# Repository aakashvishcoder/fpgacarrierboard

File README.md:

# FPGA Carrier Board

KiCad 10 design for an FPGA carrier board built around a Xilinx Artix-7
XC7A35T-FGG484.

## Status

Schematic complete, ERC clean (0 errors), BOM complete (56 lines). PCB
layout has not started yet.

## Sheets

| Sheet file | Contents |
|---|---|
| `powerrails.kicad_sch` | 4x TPS62130A regulators (1V0, 1V8, 1V2, 3V3) |
| `powerin.kicad_sch` | USB-C input, eFuse (TPS259251), protection |
| `fpgacore.kicad_sch` | XC7A35T-FGG484 (7 units A-G), MGT power filtering |
| `dcapacitors.kicad_sch` | FPGA decoupling capacitors (nested under FPGA Core) |
| `config_jtag.kicad_sch` | SPI flash (W25Q128), JTAG header, boot straps |
| `clocks.kicad_sch` | Y1 50 MHz system clock |
| `ethernet1g.kicad_sch` | RTL8211E-VB-CG PHY, RJ45 (HR911130C), Y3 25 MHz oscillator |
| `sfplane.kicad_sch` | Samtec SFPK-SL (SFP+ cage/connector kit), AC-coupling caps |
| `iobreakout.kicad_sch` | LEDs, buttons, spare-I/O header |

## Key parts (LCSC)

| Ref | Part | LCSC |
|---|---|---|
| U1-4 | TPS62130A | C337502 |
| U5 | eFuse | C527680 |
| U6 | XC7A35T-FGG484 | C6934285 |
| U7 | W25Q128 flash | C97521 |
| U8 | RTL8211E-VB-CG | C90735 |
| USB1 | USB-C connector | C456012 |
| J3 | RJ45 (HR911130C) | C50933 |
| J4 | SFPK-SL | C20691304 |
| L1-4 | Inductor | C719179 |
| Y1 | 50 MHz oscillator | C717684 |
| Y3 | 25 MHz oscillator | C669088 |
| J2 | SMA connector | C2693814 |

## Assembly split

JLC handles placement of ICs, the FPGA BGA, QFN parts, and decoupling
capacitors. Connectors, resistors, LEDs, the zener, the fuse, and test
points are hand-soldered as through-hole parts (not SMD) so they can be
assembled without reflow equipment. The 10µF/22µF bulk filter caps are
through-hole electrolytics; everything else hand-soldered is through-hole
ceramic, resistor, or LED.

## Generating the BOM

The GUI "Generate Bill of Materials" and Symbol Fields Table exporters are
unreliable in this KiCad build and can silently produce empty or partial
output. Use `kicad-cli` instead:

```bash
kicad-cli sch export bom \
  --output bom_cli.csv \
  --fields "Reference,Value,Footprint,QUANTITY,LCSC Part" \
  --labels "Reference,Value,Footprint,Qty,LCSC" \
  --group-by "Value,Footprint" \
  fpgacarrierboard.kicad_sch
```

## Libraries

Custom/imported symbol and footprint libraries live in `~/kicad-libs/`
(EasyEDA imports, Samtec parts, SFPK-SL, etc.), registered in the local
`sym-lib-table` and `fp-lib-table`.

## Next step

PCB layout: board outline, 6-layer stackup for BGA fanout and
controlled-impedance pairs (RGMII, SFP+ differential pairs), part
placement, and routing.

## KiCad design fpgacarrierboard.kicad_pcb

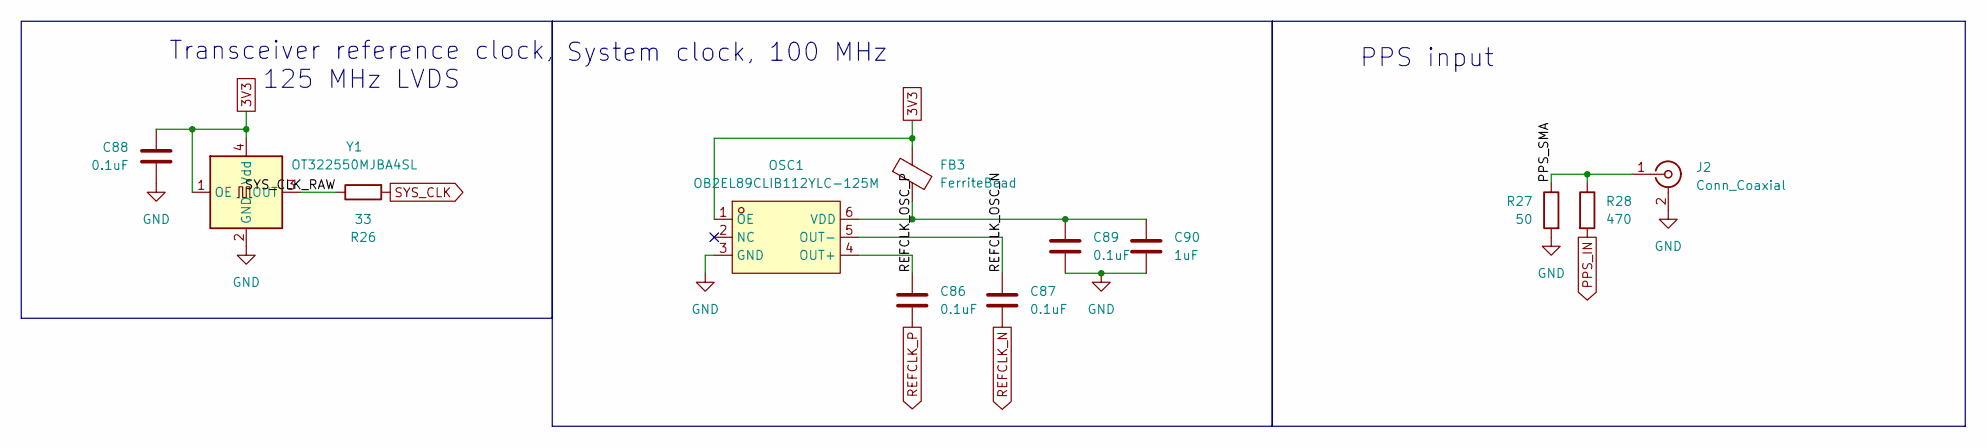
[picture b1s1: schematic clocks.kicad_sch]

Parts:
C86, C87: 0.1uF; C_0603_1608Metric; LCSC Part C14663
C88, C89: 0.1uF; C_Disc_D3.0mm_W2.0mm_P2.50mm; LCSC Part C5632430
C90: 1uF; C_Disc_D3.0mm_W2.0mm_P2.50mm; LCSC Part C1646109
FB3: FerriteBead; L_0603_1608Metric; LCSC Part C19330
J2: Conn_Coaxial; SMA_Amphenol_132134-10_Vertical; LCSC Part C2693814
OSC1: OB2EL89CLIB112YLC-125M; OSC-SMD_6P-L3.2-W2.5-BL-1; MPN OB2EL89CLIB112YLC-125M; LCSC Part C7425465
R26: 33; R_Axial_DIN0207_L6.3mm_D2.5mm_P10.16mm_Horizontal
R27: 50; R_Axial_DIN0207_L6.3mm_D2.5mm_P10.16mm_Horizontal
R28: 470; R_Axial_DIN0207_L6.3mm_D2.5mm_P10.16mm_Horizontal
Y1: OT322550MJBA4SL; OSC-SMD_4P-L3.2-W2.5-BL; LCSC Part C717684

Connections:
3V3: C88.1, FB3.1, OSC1.1 (OE), Y1.1 (OE), Y1.4 (Vdd); also elsewhere on the board
/Clocks/PPS_SMA: J2.1 (In), R27.1, R28.1
/Clocks/REFCLK_OSC_N: C87.1, OSC1.5 (OUT-)
/Clocks/REFCLK_OSC_P: C86.1, OSC1.4 (OUT+)
/Clocks/SYS_CLK_RAW: R26.1, Y1.3 (OUT)
GND: C88.2, C89.2, C90.2, J2.2 (Ext), OSC1.3 (GND), R27.2, Y1.2 (GND); also elsewhere on the board
unnamed: C89.1, C90.1, FB3.2, OSC1.6 (VDD)
PPS_IN: R28.2; also elsewhere on the board
REFCLK_N: C87.2; also elsewhere on the board
REFCLK_P: C86.2; also elsewhere on the board
SYS_CLK: R26.2; also elsewhere on the board

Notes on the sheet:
System clock, 100 MHz
PPS input
Transceiver reference clock, 125 MHz LVDS

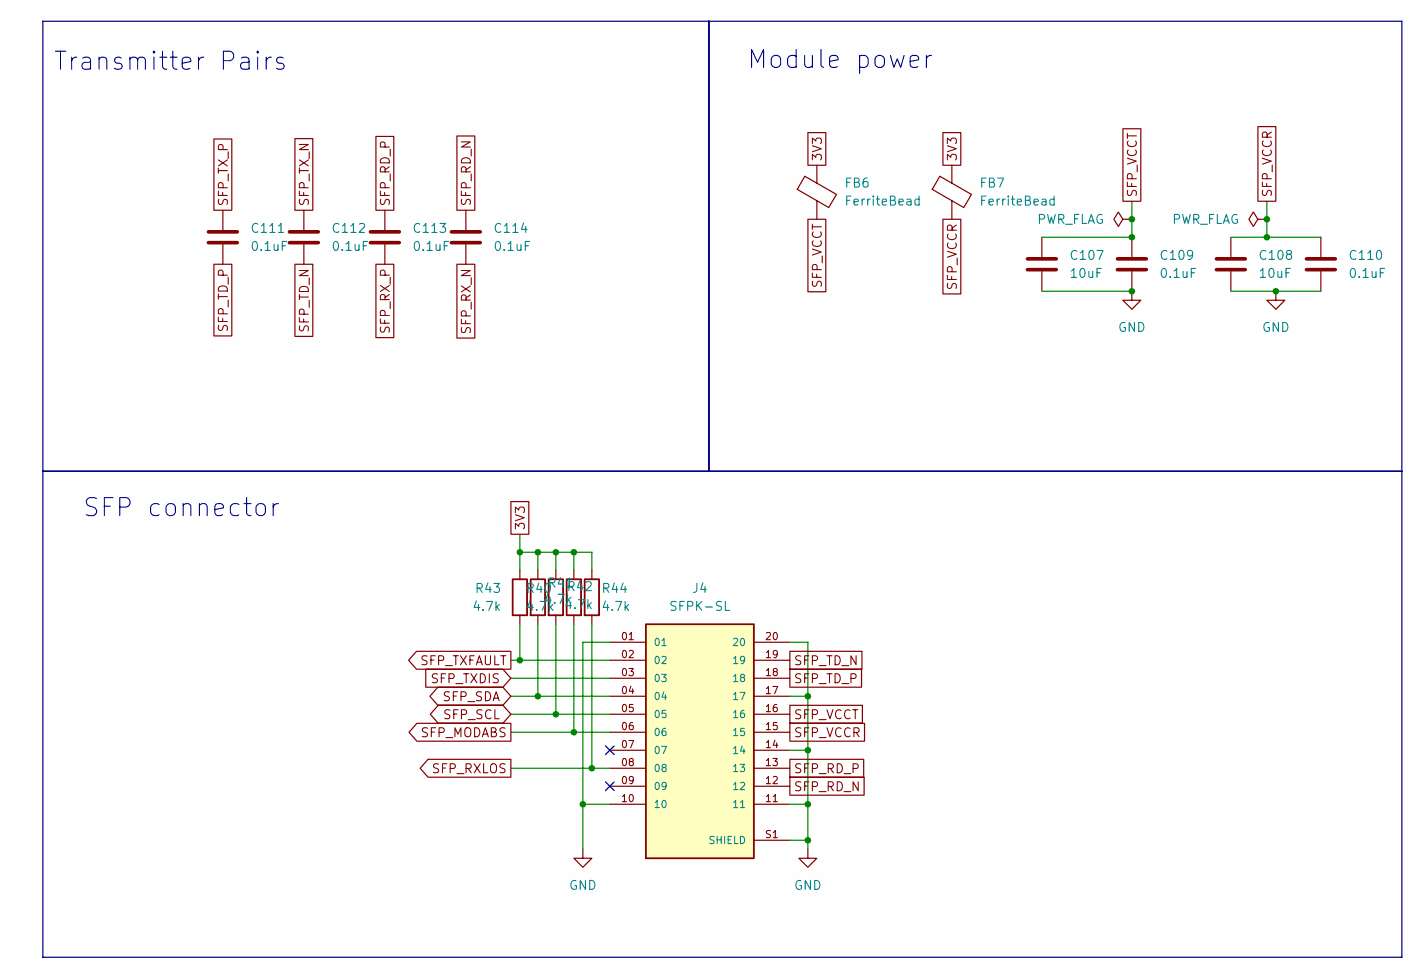
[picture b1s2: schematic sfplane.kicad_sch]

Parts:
C107, C108: 10uF; CP_Radial_D5.0mm_P2.00mm; LCSC Part C47344176
C109, C110: 0.1uF; C_Disc_D3.0mm_W2.0mm_P2.50mm; LCSC Part C5632430
C111, C112, C113, C114: 0.1uF; C_0603_1608Metric; LCSC Part C14663
FB6, FB7: FerriteBead; L_0603_1608Metric; LCSC Part C19330
J4: SFPK-SL; SAMTEC_SFPK-SL; PARTREV H; LCSC Part C20691304
R40, R41, R42, R43, R44: 4.7k; R_Axial_DIN0207_L6.3mm_D2.5mm_P10.16mm_Horizontal

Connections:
3V3: FB6.1, FB7.1, R40.1, R41.1, R42.1, R43.1, R44.1; also elsewhere on the board
GND: C107.2, C108.2, C109.2, C110.2, J4.01, J4.10, J4.11, J4.14, J4.17, J4.20, J4.S1 (SHIELD), J4.S2 (SHIELD), J4.S3 (SHIELD), J4.S4 (SHIELD), J4.S5 (SHIELD), J4.S6 (SHIELD), J4.S7 (SHIELD), J4.S8 (SHIELD), J4.S9 (SHIELD), J4.S10 (SHIELD), J4.S11 (SHIELD), J4.S12 (SHIELD), J4.S13 (SHIELD), J4.S14 (SHIELD), J4.S15 (SHIELD), J4.S16 (SHIELD), J4.S17 (SHIELD); also elsewhere on the board
SFP_MODABS: J4.06, R42.2; also elsewhere on the board
SFP_RD_N: C114.1, J4.12
SFP_RD_P: C113.1, J4.13
SFP_RXLOS: J4.08, R44.2; also elsewhere on the board
SFP_RX_N: C114.2; also elsewhere on the board
SFP_RX_P: C113.2; also elsewhere on the board
SFP_SCL: J4.05, R41.2; also elsewhere on the board
SFP_SDA: J4.04, R40.2; also elsewhere on the board
SFP_TD_N: C112.2, J4.19
SFP_TD_P: C111.2, J4.18
SFP_TXDIS: J4.03; also elsewhere on the board
SFP_TXFAULT: J4.02, R43.2; also elsewhere on the board
SFP_TX_N: C112.1; also elsewhere on the board
SFP_TX_P: C111.1; also elsewhere on the board
SFP_VCCR: C108.1, C110.1, FB7.2, J4.15
SFP_VCCT: C107.1, C109.1, FB6.2, J4.16

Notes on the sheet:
Transmitter Pairs
SFP connector
Module power

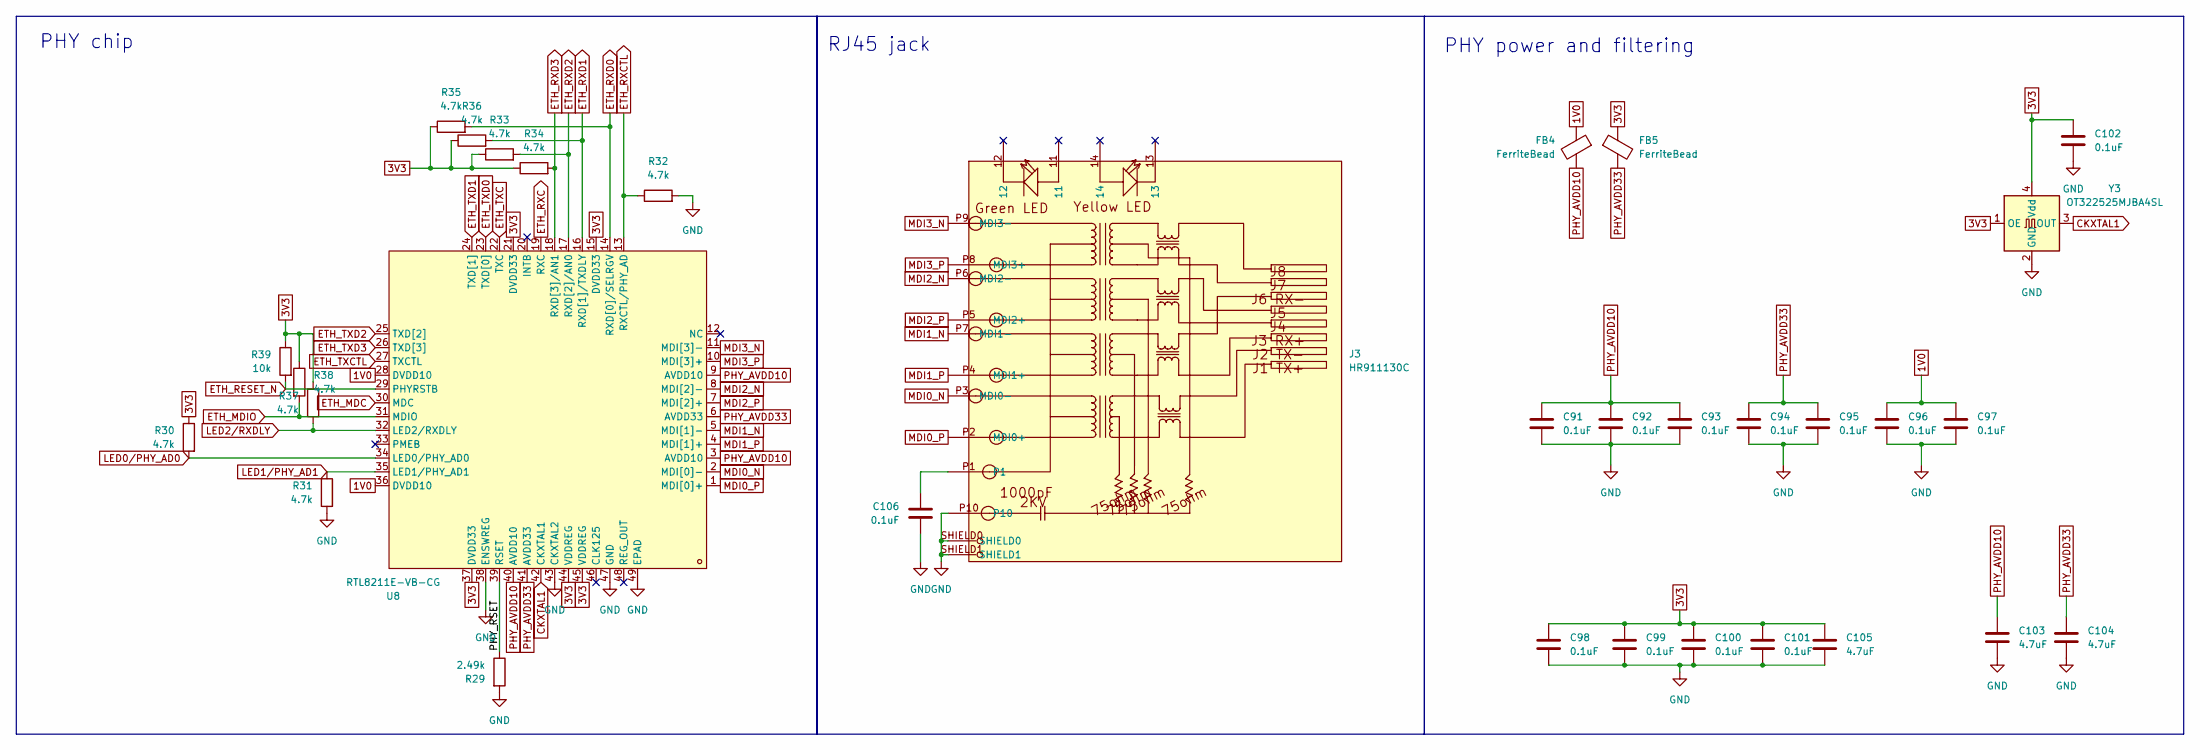
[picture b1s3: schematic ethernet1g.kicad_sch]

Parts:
C91, C92, C93, C94, C95, C96, C97, C98, C99, C100, C101, C102: 0.1uF; C_0603_1608Metric; LCSC Part C14663
C103, C104, C105: 4.7uF; C_0805_2012Metric; LCSC Part C98195
C106: 0.1uF; C_Disc_D3.0mm_W2.0mm_P2.50mm; LCSC Part C5632430
FB4, FB5: FerriteBead; L_0603_1608Metric; LCSC Part C19330
J3: HR911130C; RJ45-TH_HR911130C; MPN HR911130C; LCSC Part C50933
R29: 2.49k; R_0603_1608Metric; LCSC Part C2930072
R30, R31, R32, R33, R34, R35, R36, R37, R38: 4.7k; R_Axial_DIN0207_L6.3mm_D2.5mm_P10.16mm_Horizontal
R39: 10k; R_Axial_DIN0207_L6.3mm_D2.5mm_P10.16mm_Horizontal
U8: RTL8211E-VB-CG; QFN-48_L6.0-W6.0-P0.40-BL-EP3.8; MPN RTL8211E-VB-CG; LCSC Part C90735
Y3: OT322525MJBA4SL; OSC-SMD_4P-L3.2-W2.5-BL; LCSC Part C669088

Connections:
1V0: C96.1, C97.1, FB4.1, U8.28 (DVDD10), U8.36 (DVDD10); also elsewhere on the board
3V3: C98.1, C99.1, C100.1, C101.1, C102.1, C105.1, FB5.1, R30.1, R33.1, R34.1, R35.1, R36.1, R37.1, R38.1, R39.1, U8.15 (DVDD33), U8.21 (DVDD33), U8.37 (DVDD33), U8.44 (VDDREG), U8.45 (VDDREG), Y3.1 (OE), Y3.4 (Vdd); also elsewhere on the board
/Ethernet_1G/PHY_RSET: R29.1, U8.39 (RSET)
CKXTAL1: U8.42 (CKXTAL1), Y3.3 (OUT)
ETH_MDC: U8.30 (MDC); also elsewhere on the board
ETH_MDIO: R38.2, U8.31 (MDIO); also elsewhere on the board
ETH_RESET_N: R39.2, U8.29 (PHYRSTB); also elsewhere on the board
ETH_RXC: U8.19 (RXC); also elsewhere on the board
ETH_RXCTL: R32.1, U8.13 (RXCTL/PHY_AD); also elsewhere on the board
ETH_RXD0: R35.2, U8.14 (RXD[0]/SELRGV); also elsewhere on the board
ETH_RXD1: R36.2, U8.16 (RXD[1]/TXDLY); also elsewhere on the board
ETH_RXD2: R33.2, U8.17 (RXD[2]/AN0); also elsewhere on the board
ETH_RXD3: R34.2, U8.18 (RXD[3]/AN1); also elsewhere on the board
ETH_TXC: U8.22 (TXC); also elsewhere on the board
ETH_TXCTL: U8.27 (TXCTL); also elsewhere on the board
ETH_TXD0: U8.23 (TXD[0]); also elsewhere on the board
ETH_TXD1: U8.24 (TXD[1]); also elsewhere on the board
ETH_TXD2: U8.25 (TXD[2]); also elsewhere on the board
ETH_TXD3: U8.26 (TXD[3]); also elsewhere on the board
GND: C91.2, C92.2, C93.2, C94.2, C95.2, C96.2, C97.2, C98.2, C99.2, C100.2, C101.2, C102.2, C103.2, C104.2, C105.2, C106.2, J3.P10, J3.SHIELD0, J3.SHIELD1, R29.2, R31.2, R32.2, U8.38 (ENSWREG), U8.43 (CKXTAL2), U8.47 (GND), U8.49 (EPAD), Y3.2 (GND); also elsewhere on the board
LED0/PHY_AD0: R30.2, U8.34 (LED0/PHY_AD0)
LED1/PHY_AD1: R31.1, U8.35 (LED1/PHY_AD1)
LED2/RXDLY: R37.2, U8.32 (LED2/RXDLY)
MDI0_N: J3.P3 (MDI0-), U8.2 (MDI[0]-)
MDI0_P: J3.P2 (MDI0+), U8.1 (MDI[0]+)
MDI1_N: J3.P7 (MDI1-), U8.5 (MDI[1]-)
MDI1_P: J3.P4 (MDI1+), U8.4 (MDI[1]+)
MDI2_N: J3.P6 (MDI2-), U8.8 (MDI[2]-)
MDI2_P: J3.P5 (MDI2+), U8.7 (MDI[2]+)
MDI3_N: J3.P9 (MDI3-), U8.11 (MDI[3]-)
MDI3_P: J3.P8 (MDI3+), U8.10 (MDI[3]+)
unnamed: C106.1, J3.P1
PHY_AVDD10: C91.1, C92.1, C93.1, C103.1, FB4.2, U8.3 (AVDD10), U8.9 (AVDD10), U8.40 (AVDD10)
PHY_AVDD33: C94.1, C95.1, C104.1, FB5.2, U8.6 (AVDD33), U8.41 (AVDD33)

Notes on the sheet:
PHY chip
PHY power and filtering
RJ45 jack

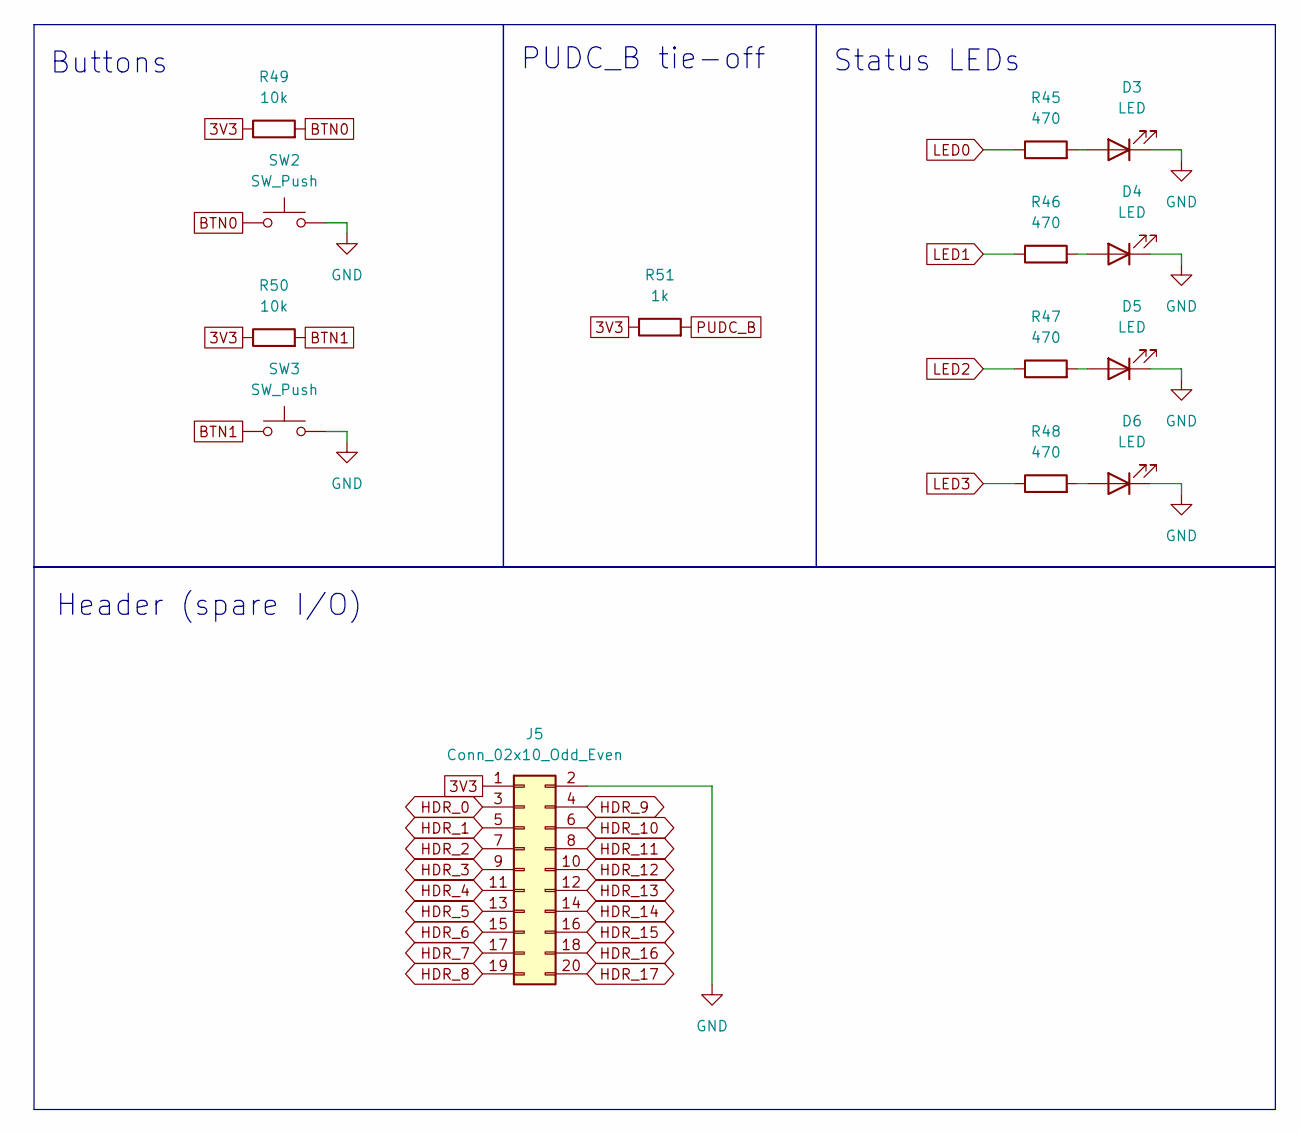
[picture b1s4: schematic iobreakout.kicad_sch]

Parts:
D3, D4, D5, D6: LED; LED_D3.0mm
J5: Conn_02x10_Odd_Even; PinHeader_2x10_P2.54mm_Vertical
R45, R46, R47, R48: 470; R_Axial_DIN0207_L6.3mm_D2.5mm_P10.16mm_Horizontal
R49, R50: 10k; R_Axial_DIN0207_L6.3mm_D2.5mm_P10.16mm_Horizontal
R51: 1k; R_Axial_DIN0207_L6.3mm_D2.5mm_P10.16mm_Horizontal
SW2, SW3: SW_Push; SW_SPST_TL3342

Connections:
3V3: J5.1, R49.1, R50.1, R51.1; also elsewhere on the board
BTN0: R49.2, SW2.1; also elsewhere on the board
BTN1: R50.2, SW3.1; also elsewhere on the board
GND: D3.1 (K), D4.1 (K), D5.1 (K), D6.1 (K), J5.2, SW2.2, SW3.2; also elsewhere on the board
HDR_0: J5.3; also elsewhere on the board
HDR_1: J5.5; also elsewhere on the board
HDR_2: J5.7; also elsewhere on the board
HDR_3: J5.9; also elsewhere on the board
HDR_4: J5.11; also elsewhere on the board
HDR_5: J5.13; also elsewhere on the board
HDR_6: J5.15; also elsewhere on the board
HDR_7: J5.17; also elsewhere on the board
HDR_8: J5.19; also elsewhere on the board
HDR_9: J5.4; also elsewhere on the board
HDR_10: J5.6; also elsewhere on the board
HDR_11: J5.8; also elsewhere on the board
HDR_12: J5.10; also elsewhere on the board
HDR_13: J5.12; also elsewhere on the board
HDR_14: J5.14; also elsewhere on the board
HDR_15: J5.16; also elsewhere on the board
HDR_16: J5.18; also elsewhere on the board
HDR_17: J5.20; also elsewhere on the board
LED0: R45.1; also elsewhere on the board
LED1: R46.1; also elsewhere on the board
LED2: R47.1; also elsewhere on the board
LED3: R48.1; also elsewhere on the board
unnamed: D3.2 (A), R45.2
unnamed: D4.2 (A), R46.2
unnamed: D5.2 (A), R47.2
unnamed: D6.2 (A), R48.2
PUDC_B: R51.2; also elsewhere on the board

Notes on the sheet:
Buttons
PUDC_B tie-off
Status LEDs
Header (spare I/O)

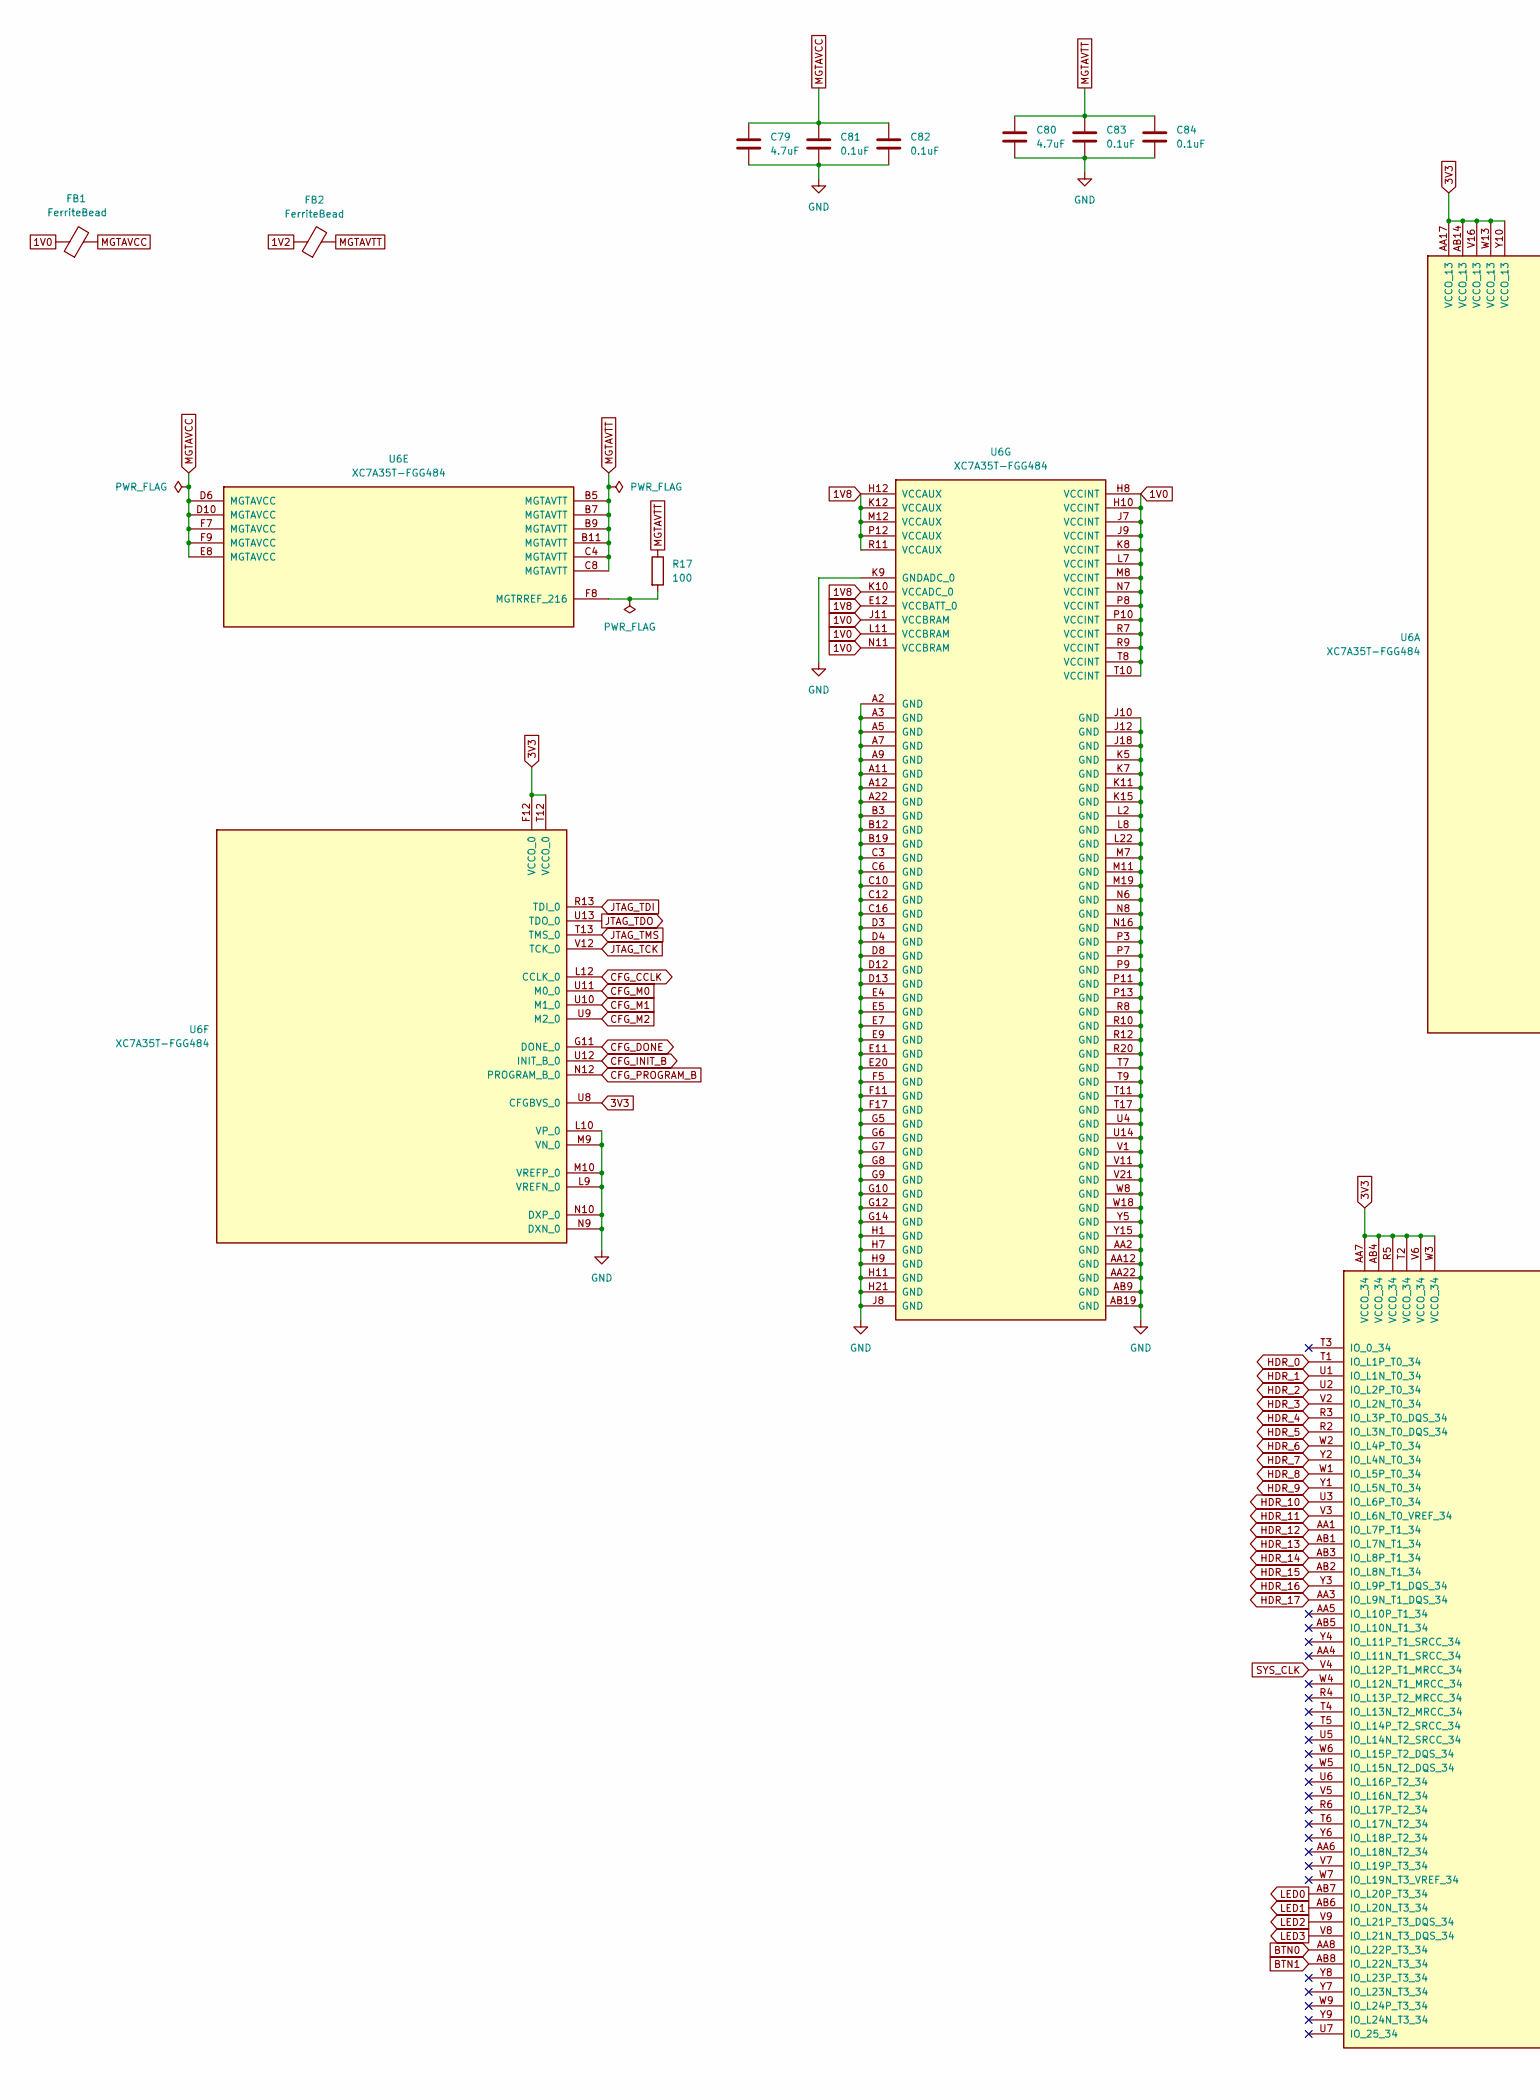
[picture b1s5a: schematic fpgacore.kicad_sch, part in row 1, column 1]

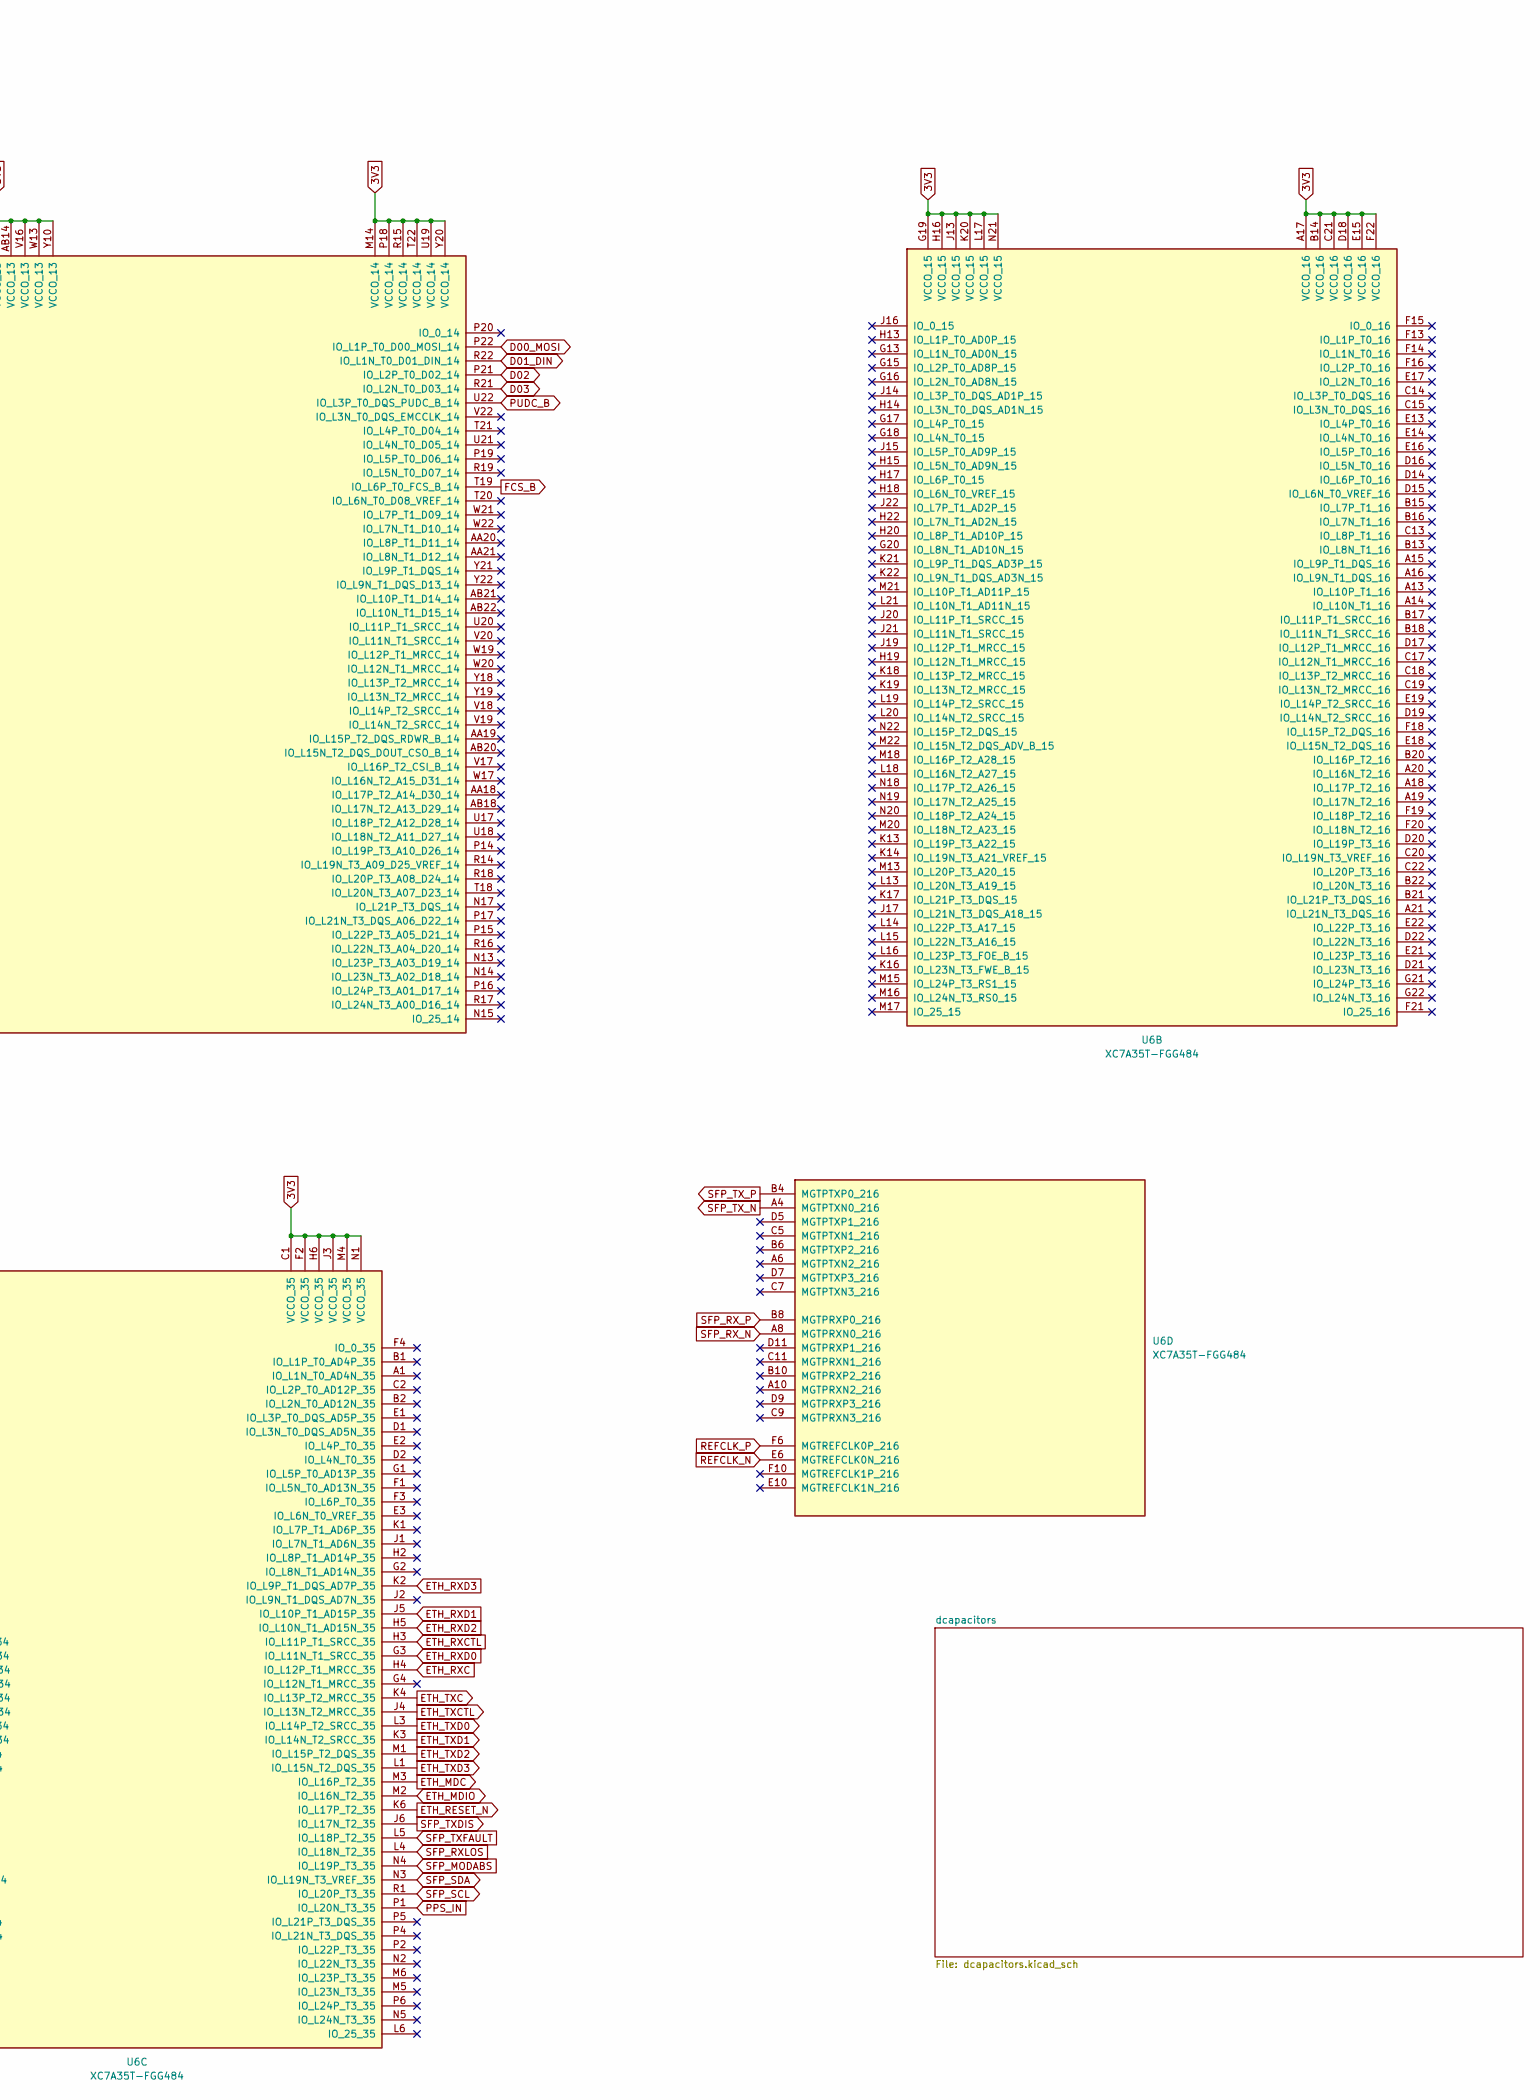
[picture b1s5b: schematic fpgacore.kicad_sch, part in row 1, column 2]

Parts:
C79, C80: 4.7uF; C_0603_1608Metric; LCSC Part C107368
C81, C82, C83, C84: 0.1uF; C_0603_1608Metric; LCSC Part C14663
FB1, FB2: FerriteBead; L_0603_1608Metric; LCSC Part C19330
R17: 100; R_0603_1608Metric; LCSC Part C2906981
U6: XC7A35T-FGG484; Xilinx_FGG484; LCSC Part C6934285

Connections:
1V0: FB1.1, U6.H8 (VCCINT), U6.H10 (VCCINT), U6.J7 (VCCINT), U6.J9 (VCCINT), U6.J11 (VCCBRAM), U6.K8 (VCCINT), U6.L7 (VCCINT), U6.L11 (VCCBRAM), U6.M8 (VCCINT), U6.N7 (VCCINT), U6.N11 (VCCBRAM), U6.P8 (VCCINT), U6.P10 (VCCINT), U6.R7 (VCCINT), U6.R9 (VCCINT), U6.T8 (VCCINT), U6.T10 (VCCINT); also elsewhere on the board
1V2: FB2.1; also elsewhere on the board
1V8: U6.E12 (VCCBATT_0), U6.H12 (VCCAUX), U6.K10 (VCCADC_0), U6.K12 (VCCAUX), U6.M12 (VCCAUX), U6.P12 (VCCAUX), U6.R11 (VCCAUX); also elsewhere on the board
3V3: U6.A17 (VCCO_16), U6.AA7 (VCCO_34), U6.AA17 (VCCO_13), U6.AB4 (VCCO_34), U6.AB14 (VCCO_13), U6.B14 (VCCO_16), U6.C1 (VCCO_35), U6.C21 (VCCO_16), U6.D18 (VCCO_16), U6.E15 (VCCO_16), U6.F2 (VCCO_35), U6.F12 (VCCO_0), U6.F22 (VCCO_16), U6.G19 (VCCO_15), U6.H6 (VCCO_35), U6.H16 (VCCO_15), U6.J3 (VCCO_35), U6.J13 (VCCO_15), U6.K20 (VCCO_15), U6.L17 (VCCO_15), U6.M4 (VCCO_35), U6.M14 (VCCO_14), U6.N1 (VCCO_35), U6.N21 (VCCO_15), U6.P18 (VCCO_14), U6.R5 (VCCO_34), U6.R15 (VCCO_14), U6.T2 (VCCO_34), U6.T12 (VCCO_0), U6.T22 (VCCO_14), U6.U8 (CFGBVS_0), U6.U19 (VCCO_14), U6.V6 (VCCO_34), U6.V16 (VCCO_13), U6.W3 (VCCO_34), U6.W13 (VCCO_13), U6.Y10 (VCCO_13), U6.Y20 (VCCO_14); also elsewhere on the board
BTN0: U6.AA8 (IO_L22P_T3_34); also elsewhere on the board
BTN1: U6.AB8 (IO_L22N_T3_34); also elsewhere on the board
CFG_CCLK: U6.L12 (CCLK_0); also elsewhere on the board
CFG_DONE: U6.G11 (DONE_0); also elsewhere on the board
CFG_INIT_B: U6.U12 (INIT_B_0); also elsewhere on the board
CFG_M0: U6.U11 (M0_0); also elsewhere on the board
CFG_M1: U6.U10 (M1_0); also elsewhere on the board
CFG_M2: U6.U9 (M2_0); also elsewhere on the board
CFG_PROGRAM_B: U6.N12 (PROGRAM_B_0); also elsewhere on the board
D00_MOSI: U6.P22 (IO_L1P_T0_D00_MOSI_14); also elsewhere on the board
D01_DIN: U6.R22 (IO_L1N_T0_D01_DIN_14); also elsewhere on the board
D02: U6.P21 (IO_L2P_T0_D02_14); also elsewhere on the board
D03: U6.R21 (IO_L2N_T0_D03_14); also elsewhere on the board
ETH_MDC: U6.M3 (IO_L16P_T2_35); also elsewhere on the board
ETH_MDIO: U6.M2 (IO_L16N_T2_35); also elsewhere on the board
ETH_RESET_N: U6.K6 (IO_L17P_T2_35); also elsewhere on the board
ETH_RXC: U6.H4 (IO_L12P_T1_MRCC_35); also elsewhere on the board
ETH_RXCTL: U6.H3 (IO_L11P_T1_SRCC_35); also elsewhere on the board
ETH_RXD0: U6.G3 (IO_L11N_T1_SRCC_35); also elsewhere on the board
ETH_RXD1: U6.J5 (IO_L10P_T1_AD15P_35); also elsewhere on the board
ETH_RXD2: U6.H5 (IO_L10N_T1_AD15N_35); also elsewhere on the board
ETH_RXD3: U6.K2 (IO_L9P_T1_DQS_AD7P_35); also elsewhere on the board
ETH_TXC: U6.K4 (IO_L13P_T2_MRCC_35); also elsewhere on the board
ETH_TXCTL: U6.J4 (IO_L13N_T2_MRCC_35); also elsewhere on the board
ETH_TXD0: U6.L3 (IO_L14P_T2_SRCC_35); also elsewhere on the board
ETH_TXD1: U6.K3 (IO_L14N_T2_SRCC_35); also elsewhere on the board
ETH_TXD2: U6.M1 (IO_L15P_T2_DQS_35); also elsewhere on the board
ETH_TXD3: U6.L1 (IO_L15N_T2_DQS_35); also elsewhere on the board
FCS_B: U6.T19 (IO_L6P_T0_FCS_B_14); also elsewhere on the board
GND: C79.2, C80.2, C81.2, C82.2, C83.2, C84.2, U6.A2 (GND), U6.A3 (GND), U6.A5 (GND), U6.A7 (GND), U6.A9 (GND), U6.A11 (GND), U6.A12 (GND), U6.A22 (GND), U6.AA2 (GND), U6.AA12 (GND), U6.AA22 (GND), U6.AB9 (GND), U6.AB19 (GND), U6.B3 (GND), U6.B12 (GND), U6.B19 (GND), U6.C3 (GND), U6.C6 (GND), U6.C10 (GND), U6.C12 (GND), U6.C16 (GND), U6.D3 (GND), U6.D4 (GND), U6.D8 (GND), U6.D12 (GND), U6.D13 (GND), U6.E4 (GND), U6.E5 (GND), U6.E7 (GND), U6.E9 (GND), U6.E11 (GND), U6.E20 (GND), U6.F5 (GND), U6.F11 (GND), U6.F17 (GND), U6.G5 (GND), U6.G6 (GND), U6.G7 (GND), U6.G8 (GND), U6.G9 (GND), U6.G10 (GND), U6.G12 (GND), U6.G14 (GND), U6.H1 (GND), U6.H7 (GND), U6.H9 (GND), U6.H11 (GND), U6.H21 (GND), U6.J8 (GND), U6.J10 (GND), U6.J12 (GND), U6.J18 (GND), U6.K5 (GND), U6.K7 (GND), U6.K9 (GNDADC_0), U6.K11 (GND), U6.K15 (GND), U6.L2 (GND), U6.L8 (GND), U6.L9 (VREFN_0), U6.L10 (VP_0), U6.L22 (GND), U6.M7 (GND), U6.M9 (VN_0), U6.M10 (VREFP_0), U6.M11 (GND), U6.M19 (GND), U6.N6 (GND), U6.N8 (GND), U6.N9 (DXN_0), U6.N10 (DXP_0), U6.N16 (GND), U6.P3 (GND), U6.P7 (GND), U6.P9 (GND), U6.P11 (GND), U6.P13 (GND), U6.R8 (GND), U6.R10 (GND), U6.R12 (GND), U6.R20 (GND), U6.T7 (GND), U6.T9 (GND), U6.T11 (GND), U6.T17 (GND), U6.U4 (GND), U6.U14 (GND), U6.V1 (GND), U6.V11 (GND), U6.V21 (GND), U6.W8 (GND), U6.W18 (GND), U6.Y5 (GND), U6.Y15 (GND); also elsewhere on the board
HDR_0: U6.T1 (IO_L1P_T0_34); also elsewhere on the board
HDR_1: U6.U1 (IO_L1N_T0_34); also elsewhere on the board
HDR_2: U6.U2 (IO_L2P_T0_34); also elsewhere on the board
HDR_3: U6.V2 (IO_L2N_T0_34); also elsewhere on the board
HDR_4: U6.R3 (IO_L3P_T0_DQS_34); also elsewhere on the board
HDR_5: U6.R2 (IO_L3N_T0_DQS_34); also elsewhere on the board
HDR_6: U6.W2 (IO_L4P_T0_34); also elsewhere on the board
HDR_7: U6.Y2 (IO_L4N_T0_34); also elsewhere on the board
HDR_8: U6.W1 (IO_L5P_T0_34); also elsewhere on the board
HDR_9: U6.Y1 (IO_L5N_T0_34); also elsewhere on the board
HDR_10: U6.U3 (IO_L6P_T0_34); also elsewhere on the board
HDR_11: U6.V3 (IO_L6N_T0_VREF_34); also elsewhere on the board
HDR_12: U6.AA1 (IO_L7P_T1_34); also elsewhere on the board
HDR_13: U6.AB1 (IO_L7N_T1_34); also elsewhere on the board
HDR_14: U6.AB3 (IO_L8P_T1_34); also elsewhere on the board
HDR_15: U6.AB2 (IO_L8N_T1_34); also elsewhere on the board
HDR_16: U6.Y3 (IO_L9P_T1_DQS_34); also elsewhere on the board
HDR_17: U6.AA3 (IO_L9N_T1_DQS_34); also elsewhere on the board
JTAG_TCK: U6.V12 (TCK_0); also elsewhere on the board
JTAG_TDI: U6.R13 (TDI_0); also elsewhere on the board
JTAG_TDO: U6.U13 (TDO_0); also elsewhere on the board
JTAG_TMS: U6.T13 (TMS_0); also elsewhere on the board
LED0: U6.AB7 (IO_L20P_T3_34); also elsewhere on the board
LED1: U6.AB6 (IO_L20N_T3_34); also elsewhere on the board
LED2: U6.V9 (IO_L21P_T3_DQS_34); also elsewhere on the board
LED3: U6.V8 (IO_L21N_T3_DQS_34); also elsewhere on the board
MGTAVCC: C79.1, C81.1, C82.1, FB1.2, U6.D6 (MGTAVCC), U6.D10 (MGTAVCC), U6.E8 (MGTAVCC), U6.F7 (MGTAVCC), U6.F9 (MGTAVCC)
MGTAVTT: C80.1, C83.1, C84.1, FB2.2, R17.1, U6.B5 (MGTAVTT), U6.B7 (MGTAVTT), U6.B9 (MGTAVTT), U6.B11 (MGTAVTT), U6.C4 (MGTAVTT), U6.C8 (MGTAVTT)
unnamed: R17.2, U6.F8 (MGTRREF_216)
PPS_IN: U6.P1 (IO_L20N_T3_35); also elsewhere on the board
PUDC_B: U6.U22 (IO_L3P_T0_DQS_PUDC_B_14); also elsewhere on the board
REFCLK_N: U6.E6 (MGTREFCLK0N_216); also elsewhere on the board
REFCLK_P: U6.F6 (MGTREFCLK0P_216); also elsewhere on the board
SFP_MODABS: U6.N4 (IO_L19P_T3_35); also elsewhere on the board
SFP_RXLOS: U6.L4 (IO_L18N_T2_35); also elsewhere on the board
SFP_RX_N: U6.A8 (MGTPRXN0_216); also elsewhere on the board
SFP_RX_P: U6.B8 (MGTPRXP0_216); also elsewhere on the board
SFP_SCL: U6.R1 (IO_L20P_T3_35); also elsewhere on the board
SFP_SDA: U6.N3 (IO_L19N_T3_VREF_35); also elsewhere on the board
SFP_TXDIS: U6.J6 (IO_L17N_T2_35); also elsewhere on the board
SFP_TXFAULT: U6.L5 (IO_L18P_T2_35); also elsewhere on the board
SFP_TX_N: U6.A4 (MGTPTXN0_216); also elsewhere on the board
SFP_TX_P: U6.B4 (MGTPTXP0_216); also elsewhere on the board
SYS_CLK: U6.V4 (IO_L12P_T1_MRCC_34); also elsewhere on the board
